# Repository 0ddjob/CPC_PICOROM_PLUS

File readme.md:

# CPC+ ROM Emulator using Raspberry Pi Pico
Based on [Matt Callow's](https://github.com/mattcallow/CPC_PICOROM) original design for the CPC.

## Current Status: UNTESTED!
- 18-Nov-2024: initial design done
- 20-Nov-2024: test PCBs on their way from PCBWAY
- 3-Dec-2024: Initial testing ... not working!  (not really a surprise)
- 12-Dec-2024: Centronics pin numbering all wrong, duh!  External ROMs on Plus machines are all logical, upper ROMs only.

## Instructions
Please refer to Matt's page for firmware & instructions on how to initialise the Pico & transfer/use Amstrad CPC ROMs.<br>
ROMs can be found [here](https://www.cpcwiki.eu/index.php/ROM_List).

## Parts
- Raspberry Pi Pico
- 50-way male Centronics connector (NorComp 111-050-113L001?)
- 2 x 6mm tactile switch (for reset)
- 5 x 1N4148 diodes

## Design
Designed using Kicad.<br>
Files, including Gerbers for production, can be found [here.](/Hardware/)<br>
Centronics connector [Kicad symbol.](/Hardware/Centronics_Connector/)  I also made a custom version with signal names on the pins (see schematic image below).<br>
Raspberry Pi Pico [Kicad symbol.](https://github.com/ncarandini/KiCad-RP-Pico)<br>
Tactile switches [Kicad symbol.](https://github.com/skiselev/my_kicad_library)<br>

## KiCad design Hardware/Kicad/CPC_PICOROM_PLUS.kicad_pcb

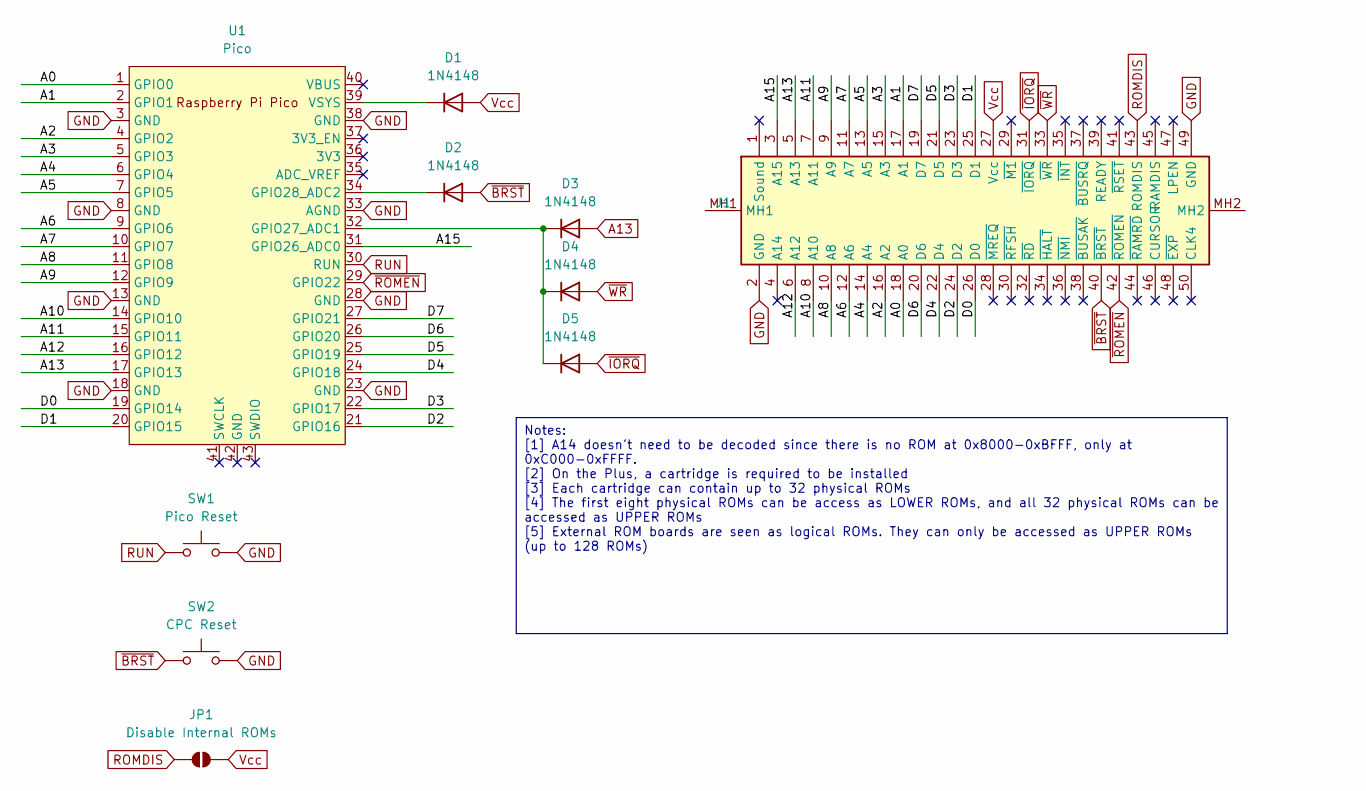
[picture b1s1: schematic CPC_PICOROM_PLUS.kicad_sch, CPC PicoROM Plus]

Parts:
D1, D2, D3, D4, D5: 1N4148; D_DO-35_SOD27_P7.62mm_Horizontal
J1: Amstrad_CPC_Plus_Expansion; 111050113L001_Amstrad_Plus; Manufacturer_Part_Number 111-050-113L001
JP1: Disable Internal ROMs; SolderJumper-2_P1.3mm_Open_RoundedPad1.0x1.5mm
SW1: Pico Reset; Switch_Tactile_6mm
SW2: CPC Reset; Switch_Tactile_6mm
U1: Pico; RPi_Pico_SMD_TH

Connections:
/A0: J1.18 (A0), U1.1 (GPIO0)
/A1: J1.17 (A1), U1.2 (GPIO1)
/A2: J1.16 (A2), U1.4 (GPIO2)
/A3: J1.15 (A3), U1.5 (GPIO3)
/A4: J1.14 (A4), U1.6 (GPIO4)
/A5: J1.13 (A5), U1.7 (GPIO5)
/A6: J1.12 (A6), U1.9 (GPIO6)
/A7: J1.11 (A7), U1.10 (GPIO7)
/A8: J1.10 (A8), U1.11 (GPIO8)
/A9: J1.9 (A9), U1.12 (GPIO9)
/A10: J1.8 (A10), U1.14 (GPIO10)
/A11: J1.7 (A11), U1.15 (GPIO11)
/A12: J1.6 (A12), U1.16 (GPIO12)
/A15: J1.3 (A15), U1.31 (GPIO26_ADC0)
/D0: J1.26 (D0), U1.19 (GPIO14)
/D1: J1.25 (D1), U1.20 (GPIO15)
/D2: J1.24 (D2), U1.21 (GPIO16)
/D3: J1.23 (D3), U1.22 (GPIO17)
/D4: J1.22 (D4), U1.24 (GPIO18)
/D5: J1.21 (D5), U1.25 (GPIO19)
/D6: J1.20 (D6), U1.26 (GPIO20)
/D7: J1.19 (D7), U1.27 (GPIO21)
A13: D3.2 (A), J1.5 (A13), U1.17 (GPIO13)
GND: J1.2 (GND), J1.49 (GND), SW1.2, SW2.2, U1.3 (GND), U1.8 (GND), U1.13 (GND), U1.18 (GND), U1.23 (GND), U1.28 (GND), U1.33 (AGND), U1.38 (GND)
unnamed: D1.1 (K), U1.39 (VSYS)
unnamed: D2.1 (K), U1.34 (GPIO28_ADC2)
unnamed: D3.1 (K), D4.1 (K), D5.1 (K), U1.32 (GPIO27_ADC1)
ROMDIS: J1.43 (ROMDIS), JP1.1 (A)
RUN: SW1.1, U1.30 (RUN)
Vcc: D1.2 (A), J1.27 (Vcc), JP1.2 (B)
~BRST: D2.2 (A), J1.40 (~BRST), SW2.1
~IORQ: D5.2 (A), J1.31 (~IORQ)
~ROMEN: J1.42 (~ROMEN), U1.29 (GPIO22)
~WR: D4.2 (A), J1.33 (~WR)

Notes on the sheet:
Notes: [1] A14 doesn't need to be decoded since there is no ROM at 0x8000-0xBFFF, only at 0xC000-0xFFFF. [2] On the Plus, a cartridge is required to be installed [3] Each cartridge can contain up to 32 physical ROMs [4] The first eight physical ROMs can be access as LOWER ROMs, and all 32 physical 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

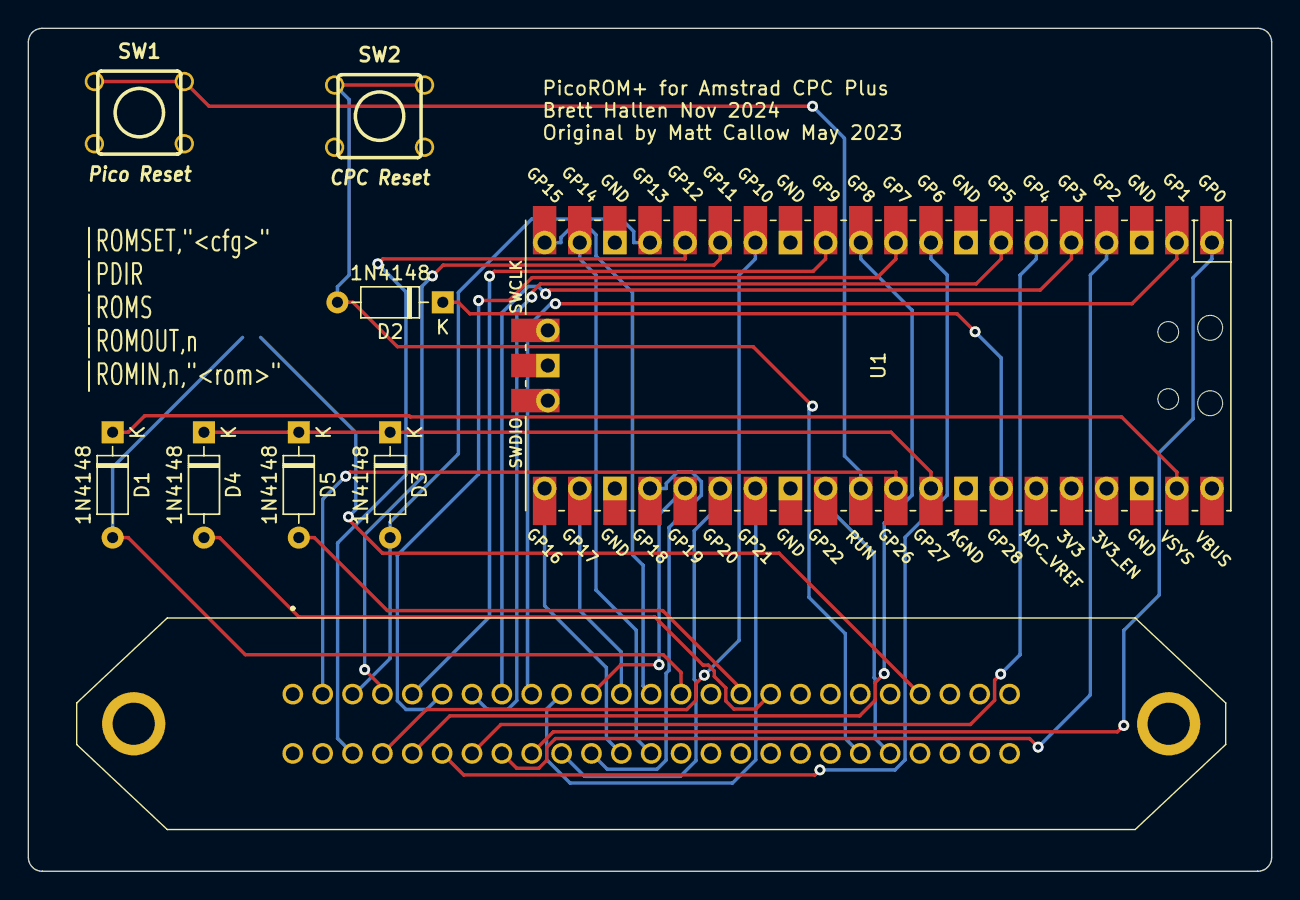
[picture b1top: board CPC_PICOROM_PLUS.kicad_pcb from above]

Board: 2 copper layers, 89.9 x 61.0 mm, 10 parts (1 on the bottom side), 34 nets.

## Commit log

2024-11-18 Centronics connector details
2024-11-18 Corrected paths
2024-11-18 Reorganised folders
2024-11-18 Minor updates to PCB
2024-11-18 PCB text updates
2024-11-18 Customised Centronics pinout for Amstrad
2024-12-03 Added ROMs
2024-12-03 Tidied up ROMs
2024-12-12 12-Dec-2024 update
2024-12-12 13-Dec-2024 updates
2024-12-12 13-Dec-2024 update
2024-12-12 Tidying files
